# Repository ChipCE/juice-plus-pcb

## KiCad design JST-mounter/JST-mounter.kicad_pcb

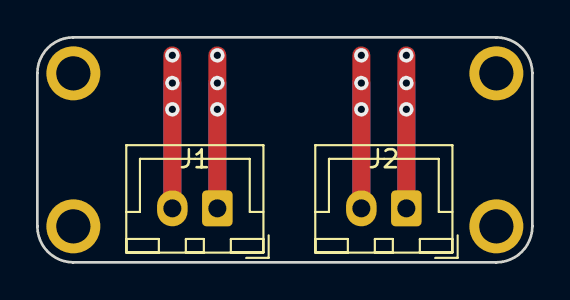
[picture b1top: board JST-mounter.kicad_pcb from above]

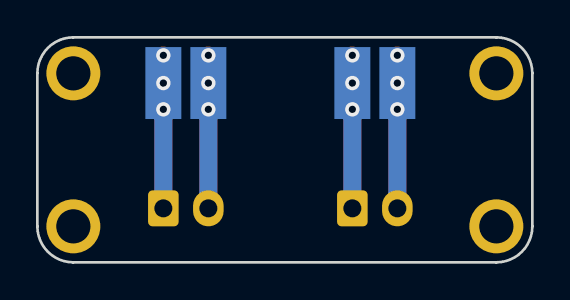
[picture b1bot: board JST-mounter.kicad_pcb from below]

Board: 2 copper layers, 27.5 x 12.5 mm, 6 parts (4 on the bottom side), 4 nets.

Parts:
J1, J2: Conn_01x02_Female; JST_XH_B02B-XH-A_1x02_P2.50mm_Vertical
J3, J4, J5, J6: Conn_01x01_Female; solder-pad

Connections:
unnamed: J1.1, J4.1
unnamed: J1.2, J3.1
unnamed: J2.1, J6.1
unnamed: J2.2, J5.1

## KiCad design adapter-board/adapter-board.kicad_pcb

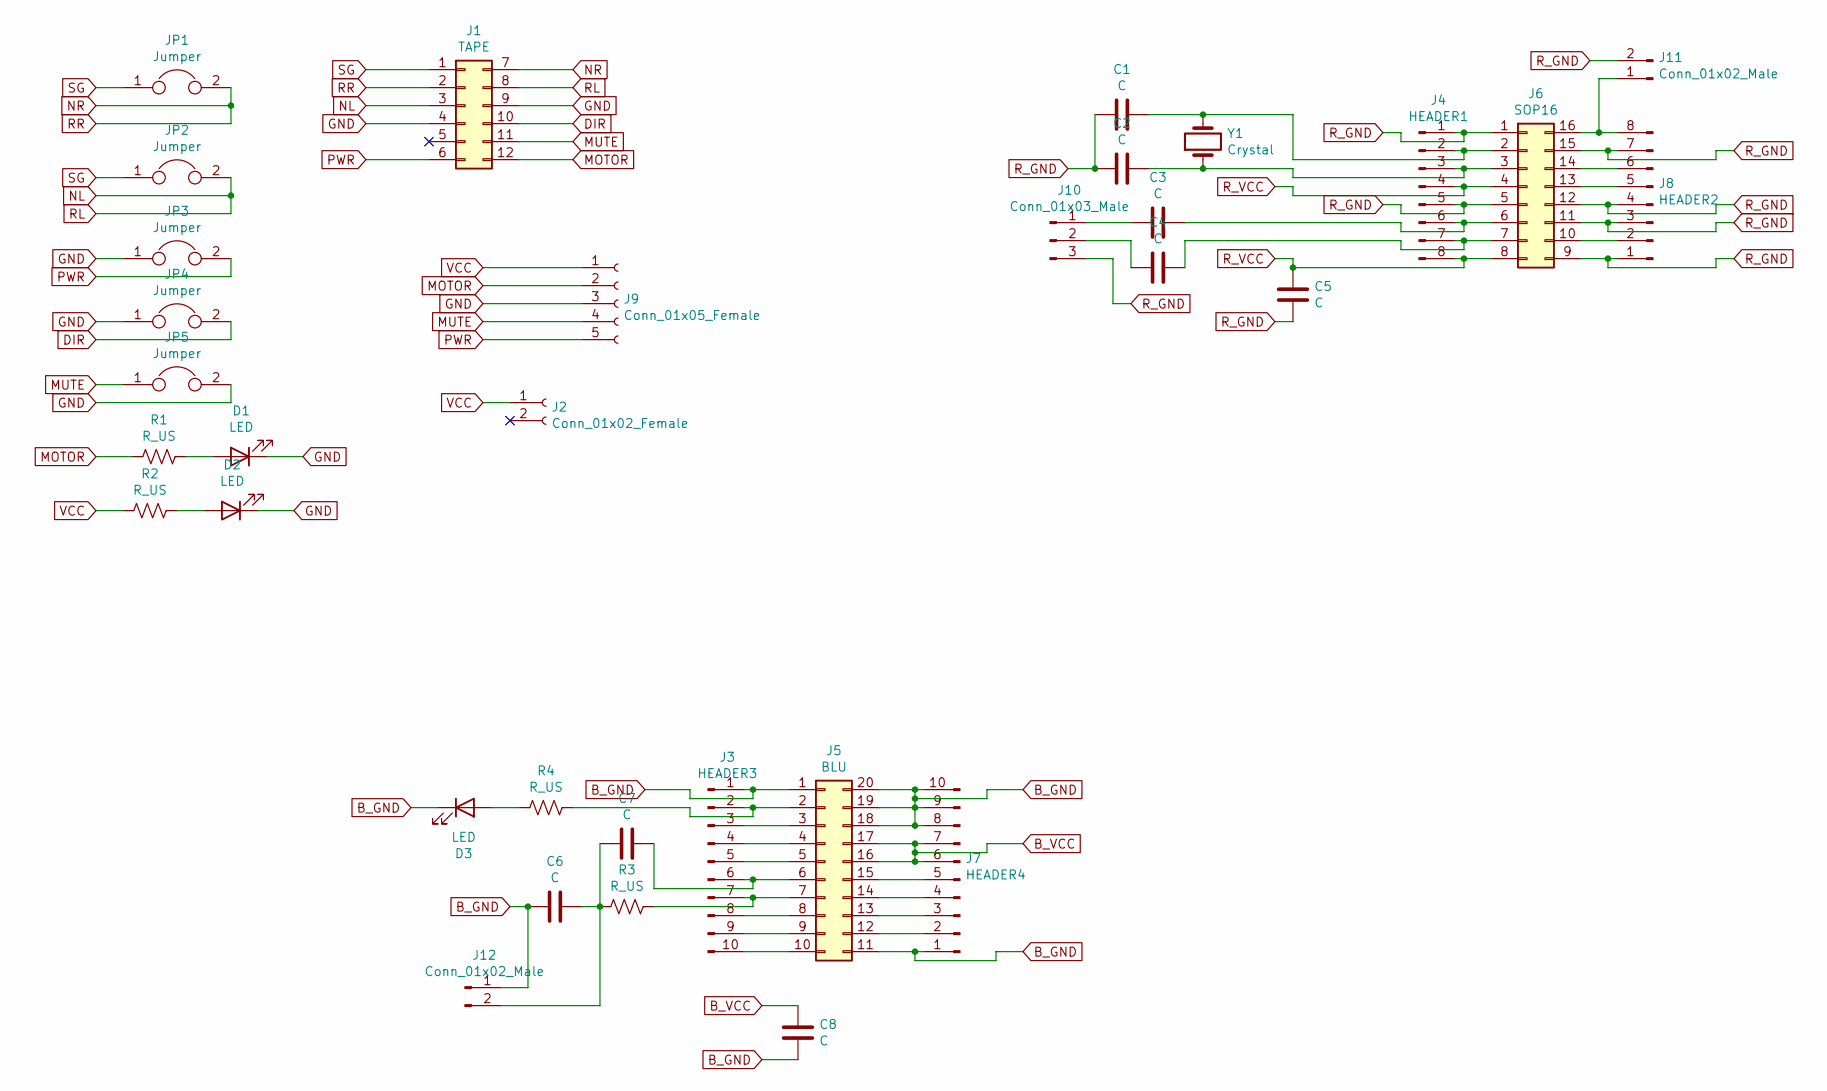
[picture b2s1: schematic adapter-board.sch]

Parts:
C1, C2, C3, C4, C5, C6, C7, C8: C; C_0805_2012Metric_Pad1.18x1.45mm_HandSolder
D1, D2, D3: LED; LED_0805_2012Metric_Pad1.15x1.40mm_HandSolder
J1: TAPE; connector-12p-offset
J2: Conn_01x02_Female; JST_XH_S2B-XH-A_1x02_P2.50mm_Horizontal
J3: HEADER3; PinHeader_1x10_P2.54mm_Vertical
J4: HEADER1; PinHeader_1x08_P2.54mm_Vertical
J5: BLU; Bluetooth_KCX_BT0003
J6: SOP16; SOP-16_4.55x10.3mm_P1.27mm
J7: HEADER4; PinHeader_1x10_P2.54mm_Vertical
J8: HEADER2; PinHeader_1x08_P2.54mm_Vertical
J9: Conn_01x05_Female; JST_XH_S5B-XH-A_1x05_P2.50mm_Horizontal
J10: Conn_01x03_Male; PinHeader_1x03_P2.54mm_Vertical
J11, J12: Conn_01x02_Male; PinHeader_1x02_P2.54mm_Vertical
JP1, JP2, JP3, JP4, JP5: Jumper; SolderJumper-2_P1.3mm_Open_RoundedPad1.0x1.5mm
R1, R2, R3, R4: R_US; R_0805_2012Metric_Pad1.20x1.40mm_HandSolder
Y1: Crystal; Crystal_C38-LF_D3.0mm_L8.0mm_Horizontal_1EP_style1

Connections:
B_GND: C6.1, C8.1, D3.1 (K), J3.1, J5.1, J5.11, J5.18, J5.19, J5.20, J7.1, J7.8, J7.9, J7.10, J12.1
B_VCC: C8.2, J5.16, J5.17, J7.6, J7.7
DIR: J1.10, JP4.2
GND: D1.1 (K), D2.1 (K), J1.4, J1.9, J9.3, JP3.1, JP4.1, JP5.2
MOTOR: J1.12, J9.2, R1.2
MUTE: J1.11, J9.4, JP5.1
NL: J1.3, J1.8, JP2.2
NR: J1.2, J1.7, JP1.2
unnamed: C1.1, J4.2, J6.2, Y1.2
unnamed: C2.1, J4.3, J6.3, Y1.1
unnamed: C3.1, J4.6, J6.6
unnamed: C3.2, J10.1
unnamed: C4.1, J4.7, J6.7
unnamed: C4.2, J10.2
unnamed: C6.2, C7.2, J12.2, R3.2
unnamed: C7.1, J3.6, J5.6
unnamed: D1.2 (A), R1.1
unnamed: D2.2 (A), R2.1
unnamed: D3.2 (A), R4.2
unnamed: J3.2, J5.2, R4.1
unnamed: J3.3, J5.3
unnamed: J3.4, J5.4
unnamed: J3.5, J5.5
unnamed: J3.7, J5.7, R3.1
unnamed: J3.8, J5.8
unnamed: J3.9, J5.9
unnamed: J3.10, J5.10
unnamed: J5.12, J7.2
unnamed: J5.13, J7.3
unnamed: J5.14, J7.4
unnamed: J5.15, J7.5
unnamed: J6.10, J8.2
unnamed: J6.13, J8.5
unnamed: J6.14, J8.6
unnamed: J6.16, J8.8, J11.1
PWR: J1.6, J9.5, JP3.2
R_GND: C1.2, C2.2, C5.1, J4.1, J4.5, J6.1, J6.5, J6.9, J6.11, J6.12, J6.15, J8.1, J8.3, J8.4, J8.7, J10.3, J11.2
R_VCC: C5.2, J4.4, J4.8, J6.4, J6.8
SG: J1.1, JP1.1, JP2.1
VCC: J2.1, J9.1, R2.2

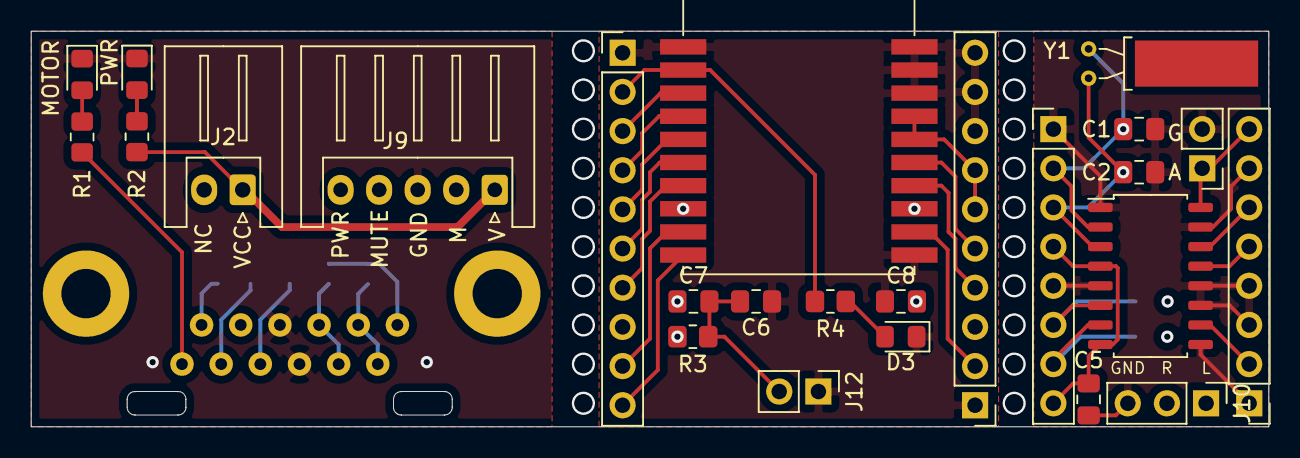
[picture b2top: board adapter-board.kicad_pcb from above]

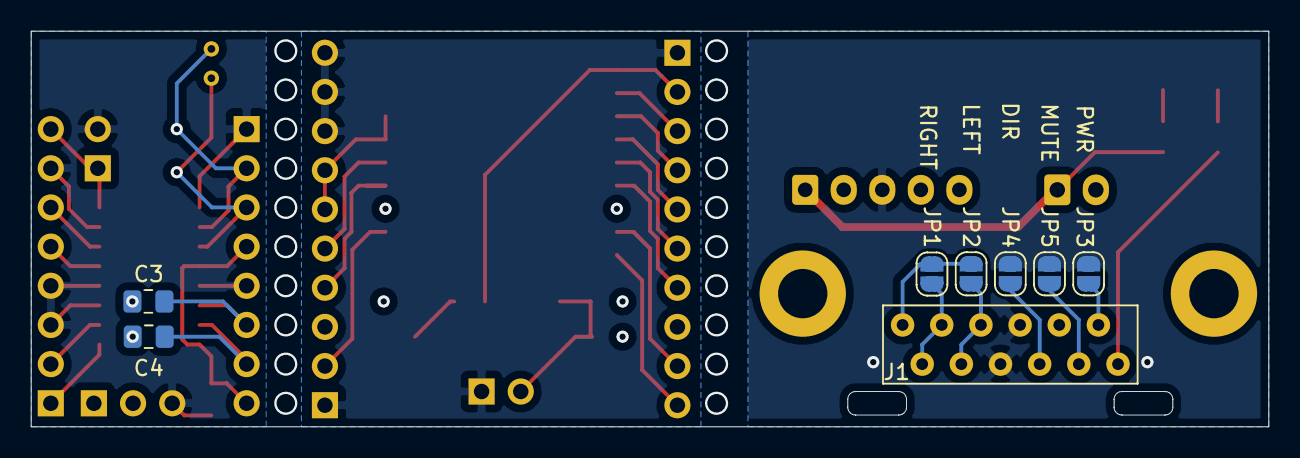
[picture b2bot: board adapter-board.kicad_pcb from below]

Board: 4 copper layers, 80.3 x 25.7 mm, 33 parts (8 on the bottom side), 40 nets.

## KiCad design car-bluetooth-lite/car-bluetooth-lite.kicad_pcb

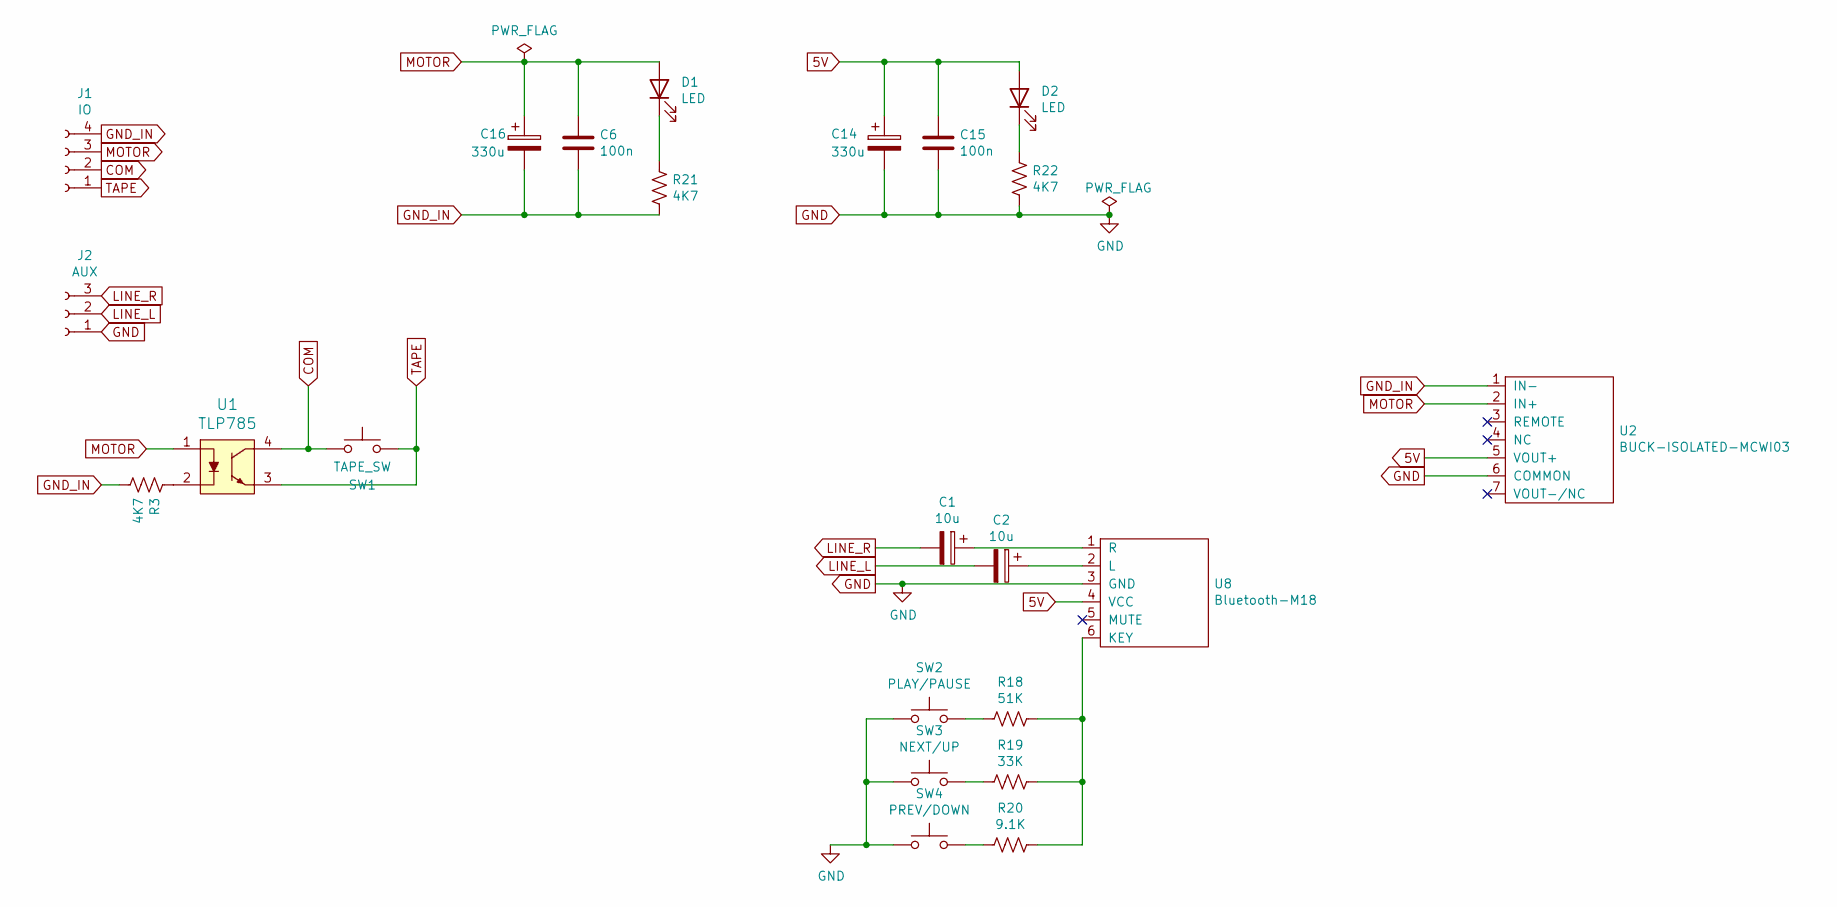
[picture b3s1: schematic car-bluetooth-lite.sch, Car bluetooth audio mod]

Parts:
C1, C2: 10u; CP_Radial_D8.0mm_P3.50mm
C6, C15: 100n; R_0805_2012Metric_Pad1.15x1.40mm_HandSolder
C14, C16: 330u; CP_Radial_D10.0mm_P5.00mm
D1, D2: LED; R_0805_2012Metric_Pad1.15x1.40mm_HandSolder
J1: IO; JST_XH_B4B-XH-A_1x04_P2.50mm_Vertical
J2: AUX; JST_XH_B3B-XH-A_1x03_P2.50mm_Vertical
R3, R21, R22: 4K7; R_0805_2012Metric_Pad1.15x1.40mm_HandSolder
R18: 51K; R_0805_2012Metric_Pad1.15x1.40mm_HandSolder
R19: 33K; R_0805_2012Metric_Pad1.15x1.40mm_HandSolder
R20: 9.1K; R_0805_2012Metric_Pad1.15x1.40mm_HandSolder
SW1: TAPE_SW; SW_Tactile_SPST_Angled_PTS645Vx83-2LFS
SW2: PLAY/PAUSE; SW_Tactile_SPST_Angled_PTS645Vx83-2LFS
SW3: NEXT/UP; SW_Tactile_SPST_Angled_PTS645Vx83-2LFS
SW4: PREV/DOWN; SW_Tactile_SPST_Angled_PTS645Vx83-2LFS
U1: TLP785; DIP-4_W7.62mm_Socket
U2: BUCK-ISOLATED-MCWI03
U8: Bluetooth-M18; Bluettoth-module-M18

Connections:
5V: C14.1, C15.1, D2.2 (A), U2.5 (VOUT+), U8.4 (VCC)
COM: J1.2, SW1.1, U1.4
GND: C14.2, C15.2, J2.1, R22.2, SW2.1, SW3.1, SW4.1, U2.6 (COMMON), U8.3 (GND)
GND_IN: C6.2, C16.2, J1.4, R3.2, R21.2, U2.1 (IN-)
LINE_L: C2.2, J2.2
LINE_R: C1.2, J2.3
MOTOR: C6.1, C16.1, D1.2 (A), J1.3, U1.1, U2.2 (IN+)
unnamed: C1.1, U8.1 (R)
unnamed: C2.1, U8.2 (L)
unnamed: D1.1 (K), R21.1
unnamed: D2.1 (K), R22.1
unnamed: R3.1, U1.2
unnamed: R18.1, R19.1, R20.1, U8.6 (KEY)
unnamed: R18.2, SW2.2
unnamed: R19.2, SW3.2
unnamed: R20.2, SW4.2
TAPE: J1.1, SW1.2, U1.3

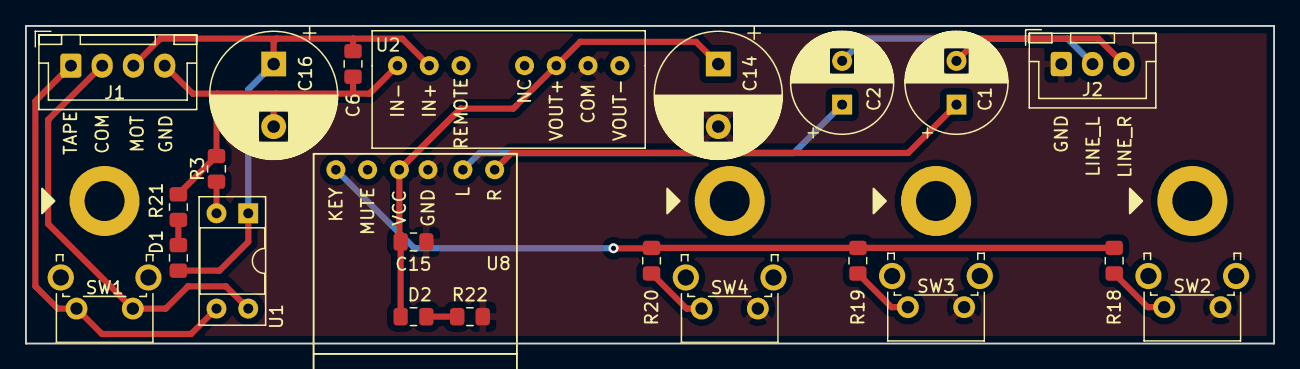
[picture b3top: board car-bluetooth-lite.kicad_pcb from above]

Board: 2 copper layers, 99.8 x 25.4 mm, 23 parts (0 on the bottom side), 17 nets.

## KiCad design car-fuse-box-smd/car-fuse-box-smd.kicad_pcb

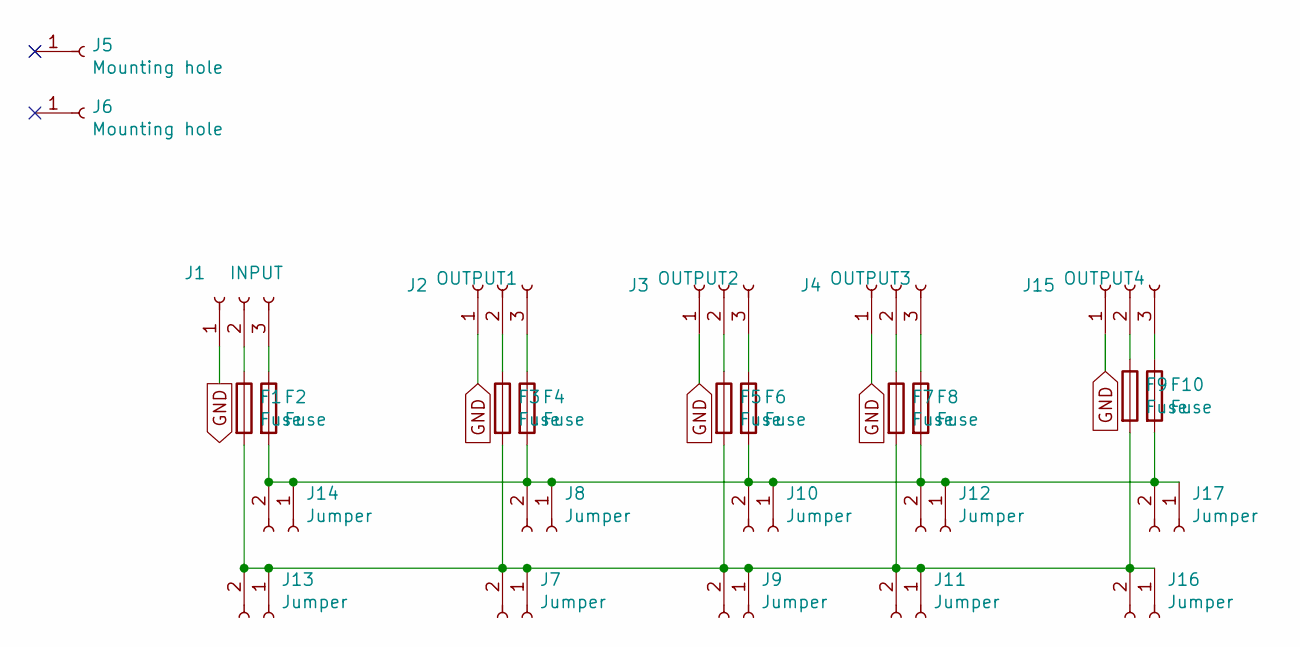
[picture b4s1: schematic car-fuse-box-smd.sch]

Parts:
F1, F2, F3, F4, F5, F6, F7, F8, F9, F10: Fuse; fuse-smd-thruhole
J1: INPUT; Molex_Micro-Fit_3.0_43650-0300_1x03_P3.00mm_Horizontal
J2: OUTPUT1; Molex_Micro-Fit_3.0_43650-0300_1x03_P3.00mm_Horizontal
J3: OUTPUT2; Molex_Micro-Fit_3.0_43650-0300_1x03_P3.00mm_Horizontal
J4: OUTPUT3; Molex_Micro-Fit_3.0_43650-0300_1x03_P3.00mm_Horizontal
J5, J6: Mounting hole; MountingHole_3.2mm_M3_DIN965_Pad
J7, J8, J9, J10, J11, J12, J13, J14, J16, J17: Jumper; jumper-wire
J15: OUTPUT4; Molex_Micro-Fit_3.0_43650-0300_1x03_P3.00mm_Horizontal

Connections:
GND: J1.1, J2.1, J3.1, J4.1, J15.1
unnamed: F1.1, J1.2
unnamed: F1.2, F3.2, F5.2, F7.2, F9.2, J7.1, J7.2, J9.1, J9.2, J11.1, J11.2, J13.1, J13.2, J16.1, J16.2
unnamed: F2.1, J1.3
unnamed: F3.1, J2.2
unnamed: F4.1, J2.3
unnamed: F5.1, J3.2
unnamed: F6.1, J3.3
unnamed: F7.1, J4.2
unnamed: F8.1, J4.3
unnamed: F9.1, J15.2
unnamed: F10.1, J15.3
unnamed: F2.2, F4.2, F6.2, F8.2, F10.2, J8.1, J8.2, J10.1, J10.2, J12.1, J12.2, J14.1, J14.2, J17.1, J17.2

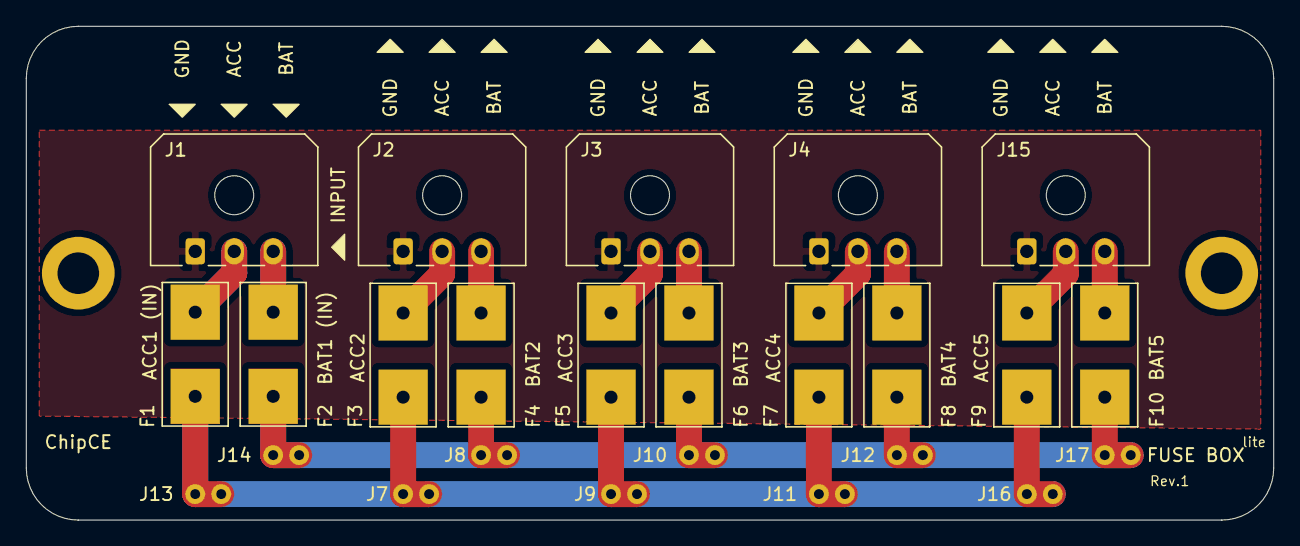
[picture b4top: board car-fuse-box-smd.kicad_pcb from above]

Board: 2 copper layers, 96.0 x 38.0 mm, 27 parts (0 on the bottom side), 13 nets.

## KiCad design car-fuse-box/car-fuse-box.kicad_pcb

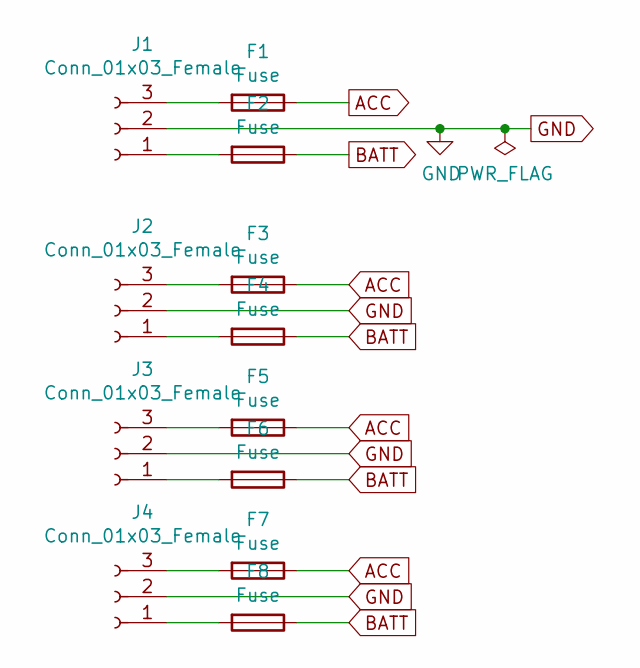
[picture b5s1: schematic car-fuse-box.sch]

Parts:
F1, F2, F3, F4, F5, F6, F7, F8: Fuse; Fuseholder_Blade_Mini_Keystone_3568
J1, J2, J3, J4: Conn_01x03_Female; TerminalBlock_RND_205-00233_1x03_P5.08mm_Horizontal

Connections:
ACC: F1.1, F3.1, F5.1, F7.1
BATT: F2.1, F4.1, F6.1, F8.1
GND: J1.2, J2.2, J3.2, J4.2
unnamed: F1.2, J1.3
unnamed: F2.2, J1.1
unnamed: F3.2, J2.3
unnamed: F4.2, J2.1
unnamed: F5.2, J3.3
unnamed: F6.2, J3.1
unnamed: F7.2, J4.3
unnamed: F8.2, J4.1

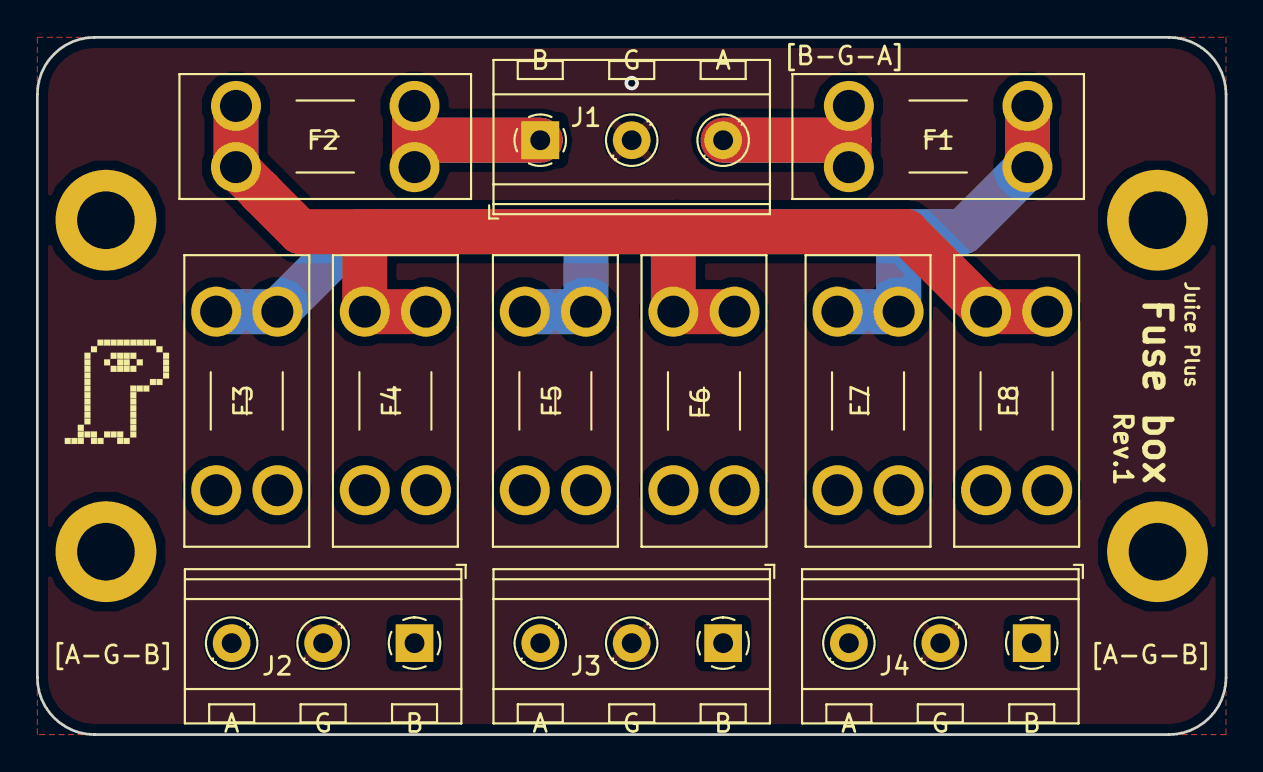
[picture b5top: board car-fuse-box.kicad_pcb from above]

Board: 4 copper layers, 66.0 x 38.7 mm, 12 parts (0 on the bottom side), 11 nets.
